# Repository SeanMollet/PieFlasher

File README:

# PieFlasher
Flash NOR and NAND flash chips quickly from a Raspberry PI. Supports 2,3,4,0,0W,0-2
Also supports integration with automated chip flashers.

## Initial setup

### The very beginning
Download the latest version of raspbian-lite and flash to an SD card.

From a freshly installed raspbian-lite

### Configure interfaces
sudo raspi-config
Go to Interfaces and enable I2C and SPI

### Install necessary tools
sudo apt install git python3-pip i2c-tools

### Check the adapter
Run i2cdetect -y 1

If all is working correctly, you'll see:
```
     0  1  2  3  4  5  6  7  8  9  a  b  c  d  e  f
00:                         -- -- -- -- -- -- -- --
10: -- -- -- -- -- -- -- -- -- -- -- -- -- -- -- --
20: -- -- -- -- -- -- -- -- -- -- -- -- -- -- -- 2f
30: -- -- -- -- -- -- -- -- -- -- -- -- 3c -- -- --
40: -- -- -- -- -- -- -- -- -- -- -- -- -- 4d -- --
50: -- -- -- -- -- -- -- -- -- -- -- -- -- -- -- --
60: -- -- -- -- -- -- -- -- -- -- -- -- -- -- -- --
70: -- -- -- -- -- -- -- --
```

### Download and build flashrom

```
git clone https://github.com/flashrom/flashrom
git checkout v.1.3.0

make -j 4
sudo make install
```

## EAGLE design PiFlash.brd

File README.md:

# PieFlasher
Flash NOR and NAND flash chips quickly from a Raspberry PI. Supports 2,3,4,0,0W,0-2
Also supports integration with automated chip flashers.

This software is not secure. The architecture is not secure. The code has some basic sanity checks, but there are countless ways it could be exploited. Don't expose it to the internet. You have been warned.

## Initial setup

### The very beginning
Download the latest version of raspbian-lite and flash to an SD card.

From a freshly installed raspbian-lite

### Configure hostname interfaces
sudo raspi-config
Go to system and then hostname and change the hostname. This name will show up in the flash interface, so make it unique for each device.
Then to go interface options and enable I2C and SPI
Use your favorite text editor to edit /boot/config.txt and edit the i2c_arm line, added the i2c_arm_baudrate part.

```
dtparam=i2c_arm=on,i2c_arm_baudrate=400000

```

Reboot the pi 

```
sudo reboot
```

### Install necessary tools
PieFlasher pre-requisites
```
sudo apt install git python3-pip i2c-tools python3-sphinx python3-venv
```

### Make a venv (Optional)
```
python3 -m venv venv
. venv/bin/activate
pip3 install -r requirements.txt
```

Luma pre-requisites
```
sudo apt install python3-dev libfreetype6-dev libjpeg-dev build-essential
sudo apt install libsdl-dev libportmidi-dev libsdl-ttf2.0-dev libsdl-mixer1.2-dev libsdl-image1.2-dev
```

### Check the adapter
Run i2cdetect -y 1

If all is working correctly, you'll see:
```
     0  1  2  3  4  5  6  7  8  9  a  b  c  d  e  f
00:                         -- -- -- -- -- -- -- --
10: -- -- -- -- -- -- -- -- -- -- -- -- -- -- -- --
20: -- -- -- -- -- -- -- -- -- -- -- -- -- -- -- 2f
30: -- -- -- -- -- -- -- -- -- -- -- -- 3c -- -- --
40: -- -- -- -- -- -- -- -- -- -- -- -- -- 4d -- --
50: -- -- -- -- -- -- -- -- -- -- -- -- -- -- -- --
60: -- -- -- -- -- -- -- -- -- -- -- -- -- -- -- --
70: -- -- -- -- -- -- -- --
```

### The files

Most files in here can be run on their own and will do something useful.

| File | Solo usage |
| gpio.py | Test GPIO inputs/outputs |
| i2c.py | Test I2C ADC and digital POT |
| manualFlash.py | Flash a chip with a given file and voltage |
| power.py | Test the adjustable power supply (DO NOT HAVE A CHIP ATTACHED!)|
| worker_client.py | Connect to server and print messages |

### Running the system

#### Server

Install the pre-requisite python packages as per above on the client devices and on a server. 

The server is run with 

```
python3 server.py
```

It will open port 5000 on all interface. Open this in a browser to see the web interface. It stores log files and image files in data/logs and data/images respectively

#### Client

The client is run with:

```
python3 worker.py
```

The first time it's run it will save a configuration file in data/config. This file specifies the url of the server. Adjust as needed. 

To run the client automatically at startup, copy pieflasher.service to /etc/systemd/system. Edit the file, changing sean and /home/sean to your respective user and path where the repo is stored. Then run:

```
systemd enable pieflasher
```

This will automatically launch PieFlasher at startup and will restart it if it were to fail.

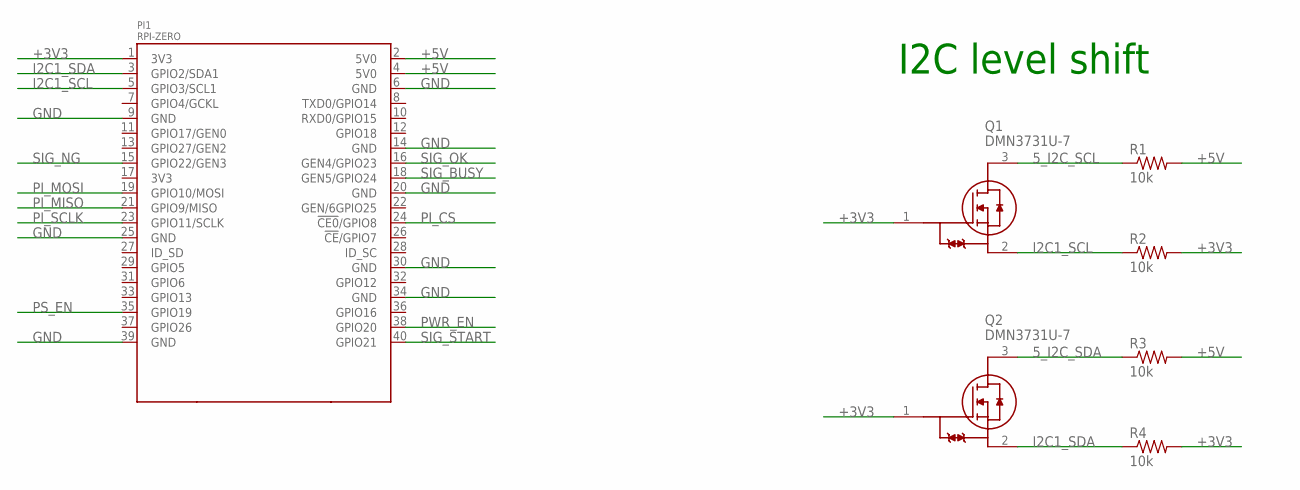
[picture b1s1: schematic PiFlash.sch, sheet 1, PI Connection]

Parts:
PI1: RPI-ZERO; RASPBERRYPI_BASTELSTUBE_V13_RASPI_BOARD_B+_FULL
Q1, Q2: DMN3731U-7; SOT96P240X110-3N
R1, R2, R3, R4: 10k; R0603

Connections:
5_I2C_SCL: Q1.3 (D), R1.1; also elsewhere on the board
5_I2C_SDA: Q2.3 (D), R3.1; also elsewhere on the board
+3V3: PI1.1 (3V3), Q1.1 (G), Q2.1 (G), R2.2, R4.2; also elsewhere on the board
+5V: PI1.2 (5V0), PI1.4 (5V0), R1.2, R3.2; also elsewhere on the board
GND: PI1.6 (GND), PI1.9 (GND), PI1.14 (GND), PI1.20 (GND), PI1.25 (GND), PI1.30 (GND), PI1.34 (GND), PI1.39 (GND); also elsewhere on the board
I2C1_SCL: PI1.5 (GPIO3/SCL1), Q1.2 (S), R2.1; also elsewhere on the board
I2C1_SDA: PI1.3 (GPIO2/SDA1), Q2.2 (S), R4.1; also elsewhere on the board
PI_CS: PI1.24 (!CE0!/GPIO8); also elsewhere on the board
PI_MISO: PI1.21 (GPIO9/MISO); also elsewhere on the board
PI_MOSI: PI1.19 (GPIO10/MOSI); also elsewhere on the board
PI_SCLK: PI1.23 (GPIO11/SCLK); also elsewhere on the board
PS_EN: PI1.35 (GPIO19); also elsewhere on the board
PWR_EN: PI1.38 (GPIO20); also elsewhere on the board
SIG_BUSY: PI1.18 (GEN5/GPIO24); also elsewhere on the board
SIG_NG: PI1.15 (GPIO22/GEN3); also elsewhere on the board
SIG_OK: PI1.16 (GEN4/GPIO23); also elsewhere on the board
SIG_START: PI1.40 (GPIO21); also elsewhere on the board

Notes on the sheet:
I2C level shift

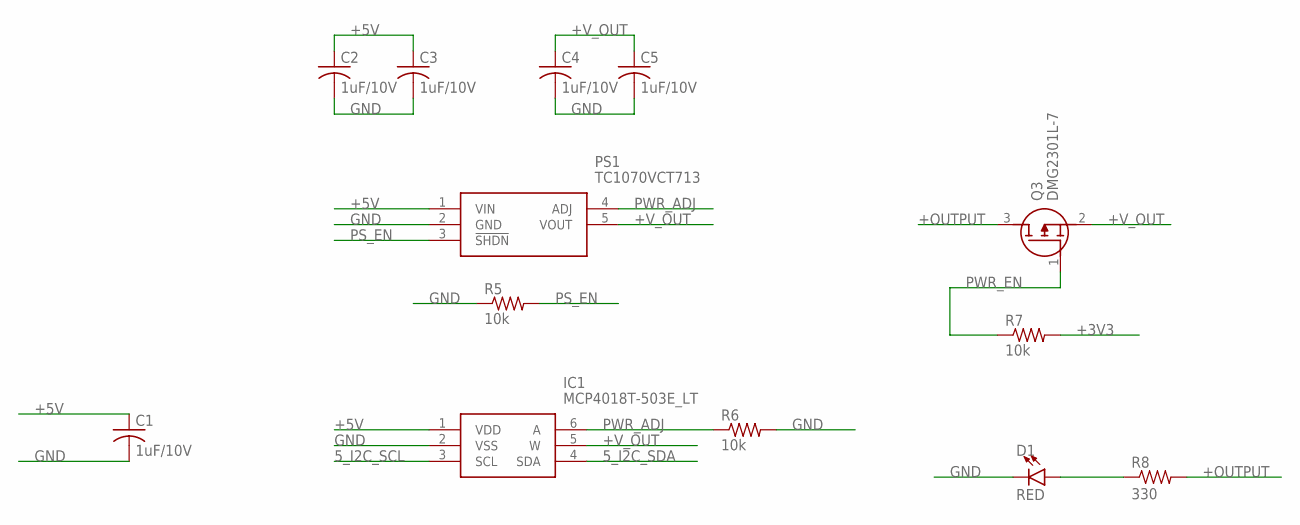
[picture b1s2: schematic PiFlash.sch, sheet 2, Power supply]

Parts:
C1, C2, C3, C4, C5: 1uF/10V; C0603
D1: RED; LED-0402
IC1: MCP4018T-503E_LT; SOT65P210X110-6N
PS1: TC1070VCT713; SOT95P280X145-5N
Q3: DMG2301L-7; SOT96P240X110-3N
R5, R6, R7: 10k; R0603
R8: 330; 0402

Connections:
5_I2C_SCL: IC1.3 (SCL); also elsewhere on the board
5_I2C_SDA: IC1.4 (SDA); also elsewhere on the board
+3V3: R7.2; also elsewhere on the board
+5V: C1.1, C2.1, C3.1, IC1.1 (VDD), PS1.1 (VIN); also elsewhere on the board
+OUTPUT: Q3.3 (D), R8.2; also elsewhere on the board
+V_OUT: C4.1, C5.1, IC1.5 (W), PS1.5 (VOUT), Q3.2 (S); also elsewhere on the board
GND: C1.2, C2.2, C3.2, C4.2, C5.2, D1.C, IC1.2 (VSS), PS1.2 (GND), R5.1, R6.2; also elsewhere on the board
unnamed: D1.A, R8.1
PS_EN: PS1.3 (!SHDN), R5.2; also elsewhere on the board
PWR_ADJ: IC1.6 (A), PS1.4 (ADJ), R6.1
PWR_EN: Q3.1 (G), R7.1; also elsewhere on the board

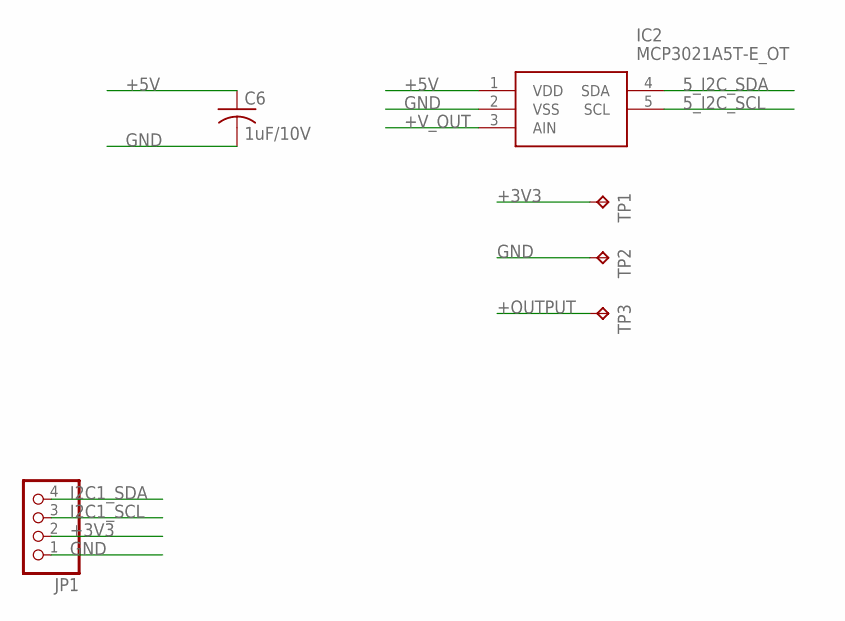
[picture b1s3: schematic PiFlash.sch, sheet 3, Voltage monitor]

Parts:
C6: 1uF/10V; C0603
IC2: MCP3021A5T-E_OT; SOT95P280X145-5N
JP1: PINHD-1X41X04_RND; 1X04_SMALL
TP1: +3v3; TP16R
TP2, TP3: TPTP16R; TP16R

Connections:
5_I2C_SCL: IC2.5 (SCL); also elsewhere on the board
5_I2C_SDA: IC2.4 (SDA); also elsewhere on the board
+3V3: JP1.2, TP1.TP; also elsewhere on the board
+5V: C6.1, IC2.1 (VDD); also elsewhere on the board
+OUTPUT: TP3.TP; also elsewhere on the board
+V_OUT: IC2.3 (AIN); also elsewhere on the board
GND: C6.2, IC2.2 (VSS), JP1.1, TP2.TP; also elsewhere on the board
I2C1_SCL: JP1.3; also elsewhere on the board
I2C1_SDA: JP1.4; also elsewhere on the board

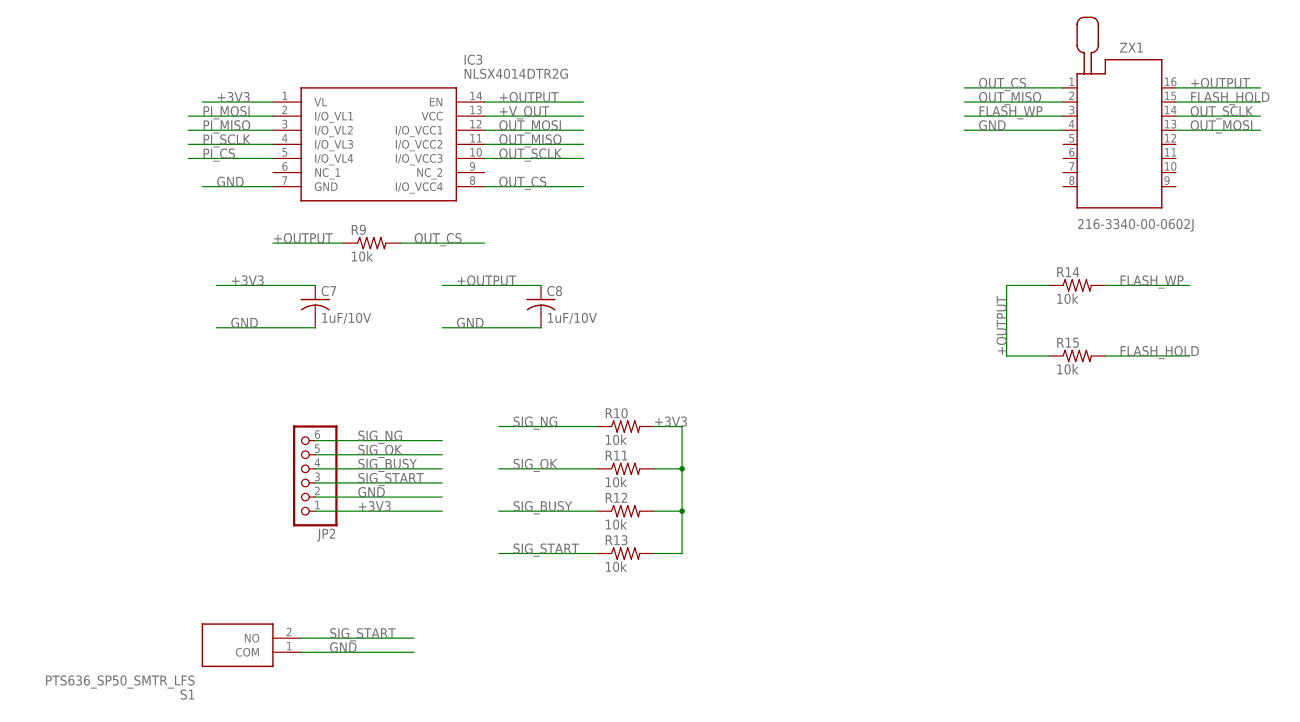
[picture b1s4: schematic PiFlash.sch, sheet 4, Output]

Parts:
C7, C8: 1uF/10V; C0603
IC3: NLSX4014DTR2G; SOP65P640X120-14N
JP2: PINHD-1X6; 1X06
R9, R10, R11, R12, R13, R14, R15: 10k; R0603
S1: PTS636_SP50_SMTR_LFS; PTS636SP50SMTRLFS
ZX1: 216-3340-00-0602J

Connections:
+3V3: C7.1, IC3.1 (VL), JP2.1, R10.2, R11.2, R12.2, R13.2; also elsewhere on the board
+OUTPUT: C8.1, IC3.14 (EN), R9.1, R14.1, R15.1, ZX1.16; also elsewhere on the board
+V_OUT: IC3.13 (VCC); also elsewhere on the board
FLASH_HOLD: R15.2, ZX1.15
FLASH_WP: R14.2, ZX1.3
GND: C7.2, C8.2, IC3.7 (GND), JP2.2, S1.1 (COM), ZX1.4; also elsewhere on the board
OUT_CS: IC3.8 (I/O_VCC4), R9.2, ZX1.1
OUT_MISO: IC3.11 (I/O_VCC2), ZX1.2
OUT_MOSI: IC3.12 (I/O_VCC1), ZX1.13
OUT_SCLK: IC3.10 (I/O_VCC3), ZX1.14
PI_CS: IC3.5 (I/O_VL4); also elsewhere on the board
PI_MISO: IC3.3 (I/O_VL2); also elsewhere on the board
PI_MOSI: IC3.2 (I/O_VL1); also elsewhere on the board
PI_SCLK: IC3.4 (I/O_VL3); also elsewhere on the board
SIG_BUSY: JP2.4, R12.1; also elsewhere on the board
SIG_NG: JP2.6, R10.1; also elsewhere on the board
SIG_OK: JP2.5, R11.1; also elsewhere on the board
SIG_START: JP2.3, R13.1, S1.2 (NO); also elsewhere on the board

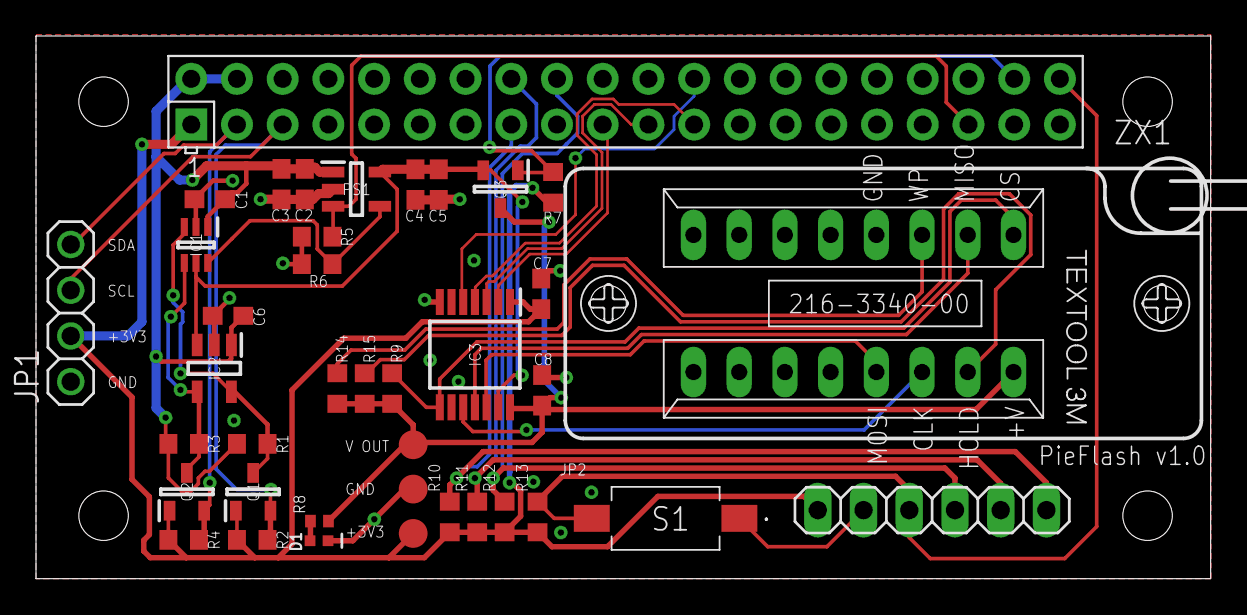
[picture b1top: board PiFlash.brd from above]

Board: 2 copper layers, 65.3 x 30.1 mm, 39 parts (0 on the bottom side), 27 nets.

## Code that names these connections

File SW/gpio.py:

#!/usr/bin/env python3
import RPi.GPIO as GPIO
import threading
from time import sleep
from typing import Callable


class pi_gpio:
    def __init__(self) -> None:
        GPIO.setmode(GPIO.BCM)
        # ("Pin name", GPIO #, Initial value)
        self.pins = {}
        self.pins["SIG_NG"] = (22, True, GPIO.OUT)
        self.pins["SIG_OK"] = (23, True, GPIO.OUT)
        self.pins["SIG_BUSY"] = (24, True, GPIO.OUT)
        self.pins["SIG_START"] = (21, True, GPIO.IN)
        self.pins["PS_EN"] = (19, False, GPIO.OUT)
        self.pins["PWR_EN"] = (20, True, GPIO.OUT)

        for name in self.pins:
            pin = self.pins[name]
            # print("Setting up",name,"GPIO:",pin[0],"default:",pin[1])
            if pin[2] == GPIO.OUT:
                GPIO.setup(pin[0], GPIO.OUT)
                GPIO.output(pin[0], pin[1])
            else:
                GPIO.setup(pin[0], GPIO.IN, pull_up_down=GPIO.PUD_UP)

    def setPin(self, pin: str, value: bool):
        if self.pins[pin] is not None and self.pins[pin][2] == GPIO.OUT:
            GPIO.output(self.pins[pin][0], value)

    def getPin(self, pin: str) -> bool:
        if self.pins[pin] is not None and self.pins[pin][2] == GPIO.IN:
            return GPIO.input(self.pins[pin][0])

    def waitForEdge(self, pin: str, state: bool) -> None:
        if self.pins[pin] is not None and self.pins[pin][2] == GPIO.IN:
            if state:
                return GPIO.wait_for_edge(self.pins[pin][0], GPIO.RISING)
            else:
                return GPIO.wait_for_edge(self.pins[pin][0], GPIO.FALLING)

    def callOnEdge(self, pin: str, state: bool, callback: Callable) -> None:
        if self.pins[pin] is not None and self.pins[pin][2] == GPIO.IN:
            if state:
                GPIO.add_event_detect(
                    self.pins[pin][0],
                    GPIO.RISING,
                    callback=callback,
                    bouncetime=300,
                )
            else:
                GPIO.add_event_detect(
                    self.pins[pin][0],
                    GPIO.FALLING,
                    callback=callback,
                    bouncetime=300,
                )

    def defaultPin(self, pin: str):
        if self.pins[pin] is not None:
            GPIO.output(self.pins[pin][0], self.pins[pin][1])

    def pinIsOutput(self, pin: str) -> bool:
        if self.pins[pin] is not None:
            return self.pins[pin][2] == GPIO.OUT
        return False

    def setSigNG(self, value: bool) -> None:
        self.setPin("SIG_NG", value)

    def setSigOK(self, value: bool) -> None:
        self.setPin("SIG_OK", value)

    def setSigBusy(self, value: bool) -> None:
        self.setPin("SIG_BUSY", value)

    def getSigStart(self) -> None:
        return self.getPin("SIG_START")

    def setPsEn(self, value: bool) -> None:
        self.setPin("PS_EN", value)

    def setPwrEn(self, value: bool) -> None:
        self.setPin("PWR_EN", not value)

    def holdSignalWorker(self, signal, delay):
        self.setPin(signal, False)
        sleep(delay)
        self.setPin(signal, True)

    def holdSignal(self, signal, delay) -> None:
        threading.Thread(target=self.holdSignalWorker, args=[signal, delay]).start()

    def waitSigStart(self) -> None:
        self.waitForEdge("SIG_START", False)

    def callOnSigStart(self, callback: Callable) -> None:
        self.callOnEdge("SIG_START", False, callback)


if __name__ == "__main__":
    print("Initializing GPIO")
    gpio = pi_gpio()

    print("IO pin testing")
    pins = ["SIG_NG", "SIG_OK", "SIG_BUSY", "SIG_START"]
    for pin in pins:
        if gpio.pinIsOutput(pin):
            print("Setting", pin, "high, press enter to lower")
            gpio.setPin(pin, True)
            input()
            print("Press enter to set", pin, "low")
            input()
            gpio.setPin(pin, False)
            print("Press enter to continue")
            input()
            gpio.defaultPin(pin)
        else:
            value = gpio.getPin(pin)
            print("Value of", pin, "is:", value, "Press enter to check again")
            input()
            value = gpio.getPin(pin)
            print("Value of", pin, "is:", value, "Press enter to continue")

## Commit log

2023-07-23 Initial checkin
2023-07-23 Added GPL 2 license
2023-07-23 Creating readme
2023-07-23 Rename readme so it renders as markdown
2023-07-23 Update readme, add first software files
2023-07-23 Adding gpio
2023-07-23 Can read the Analog and set the pot. HW works as intended
2023-07-23 Checking the output control transistor. It doesn't work. :( Oh well, ps_en works a mint, so we'll just use that
2023-07-23 Remove that test. We know it doesn't work.
2023-07-23 Removed debugging from gpio Added power, which turns on 3.3 and was used to test with a real chip (worked) Also, the +OUTPUT fet does work as long as +VOUT isn't too high (below about 4V). That's goo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
2023-07-23 Add a data folder and a .keep
2023-07-23 Don't commit things in the data directory
2023-07-23 Hide the inverted nature of Power enable
2023-07-23 Switch to CamelCase, adjust PowerEn to work the new way
2023-07-23 Split up power into testing functions
2023-07-23 Basic configuration loader/saver
2023-07-23 Add shebang to startup, add flask
2023-07-23 Add a tolerance to voltages
2023-07-23 Ignore Joe's backup files
2023-07-23 Add a mutex to i2c. Will have to add the oled to this as well
2023-07-23 Finish name change
2023-07-23 We now have a handy power supply tester in power.py, no need to also have it in i2c
2023-07-23 Add a few more comments to power.py
2023-07-23 Remove the .keep, I can just create the folders as needed
2023-07-23 Add another launch for testing
2023-07-23 Flash file that interacts with flashrom
2023-07-23 Command line flashing
2023-07-23 Utilities file
2023-07-23 Minor refactors and fixing exception handling
2023-07-23 Create the folder structure on the fly
2023-07-23 Add socketio
2023-07-23 Use the config path for config files!
2023-07-24 Add logfile names
2023-07-24 Up the SPI speed, track size
2023-07-24 Make manualflash actually work
2023-07-24 When a logfile is ordered, spawn a thread that reads/parses it. This will update percentages, process, etc..
2023-07-24 Formatted
2023-07-24 Testing to see how often we receive
2023-07-24 Reformat a little Non blocking works like a champ, we see the progress. So, we can have a nice progress bar
2023-07-24 Format the others
2023-07-24 Added a progress bar to manualFlash based on output of Flashrom. Works for erasing and flashing. So nice to have a bar...
2023-07-24 Added voltage calibration spreadsheet
2023-07-24 Oled now uses the i2c mutex Neat little display shaping up
2023-07-24 Initial testing/setup of the working and the Oled
2023-07-24 Startup logo
2023-07-24 Fix vertical scaling on the pie
2023-07-24 Fix SIG_START
2023-07-24 Take command line options for file and voltage
2023-07-24 Change to using ImageDraw for the main render, so it can also use lockI2C
2023-07-24 Scroll the filename, looks slick!
2023-07-24 Flashing works on the screen!
2023-07-24 Added tracking of reading and verifying statuses. Works pretty darn good. Now to the web interface
2023-07-24 Webserver - WIP
2023-07-24 Don't install the PI stuff on a non-Linux box. This might need to be made smarter later. Good enough for now
2023-07-24 Add websocket client
2023-07-24 WS testing works very well. I'm impressed with how well socket-io and the python WS client work.
2023-07-24 Make the worker client work. Impressive how well it does work..
2023-07-24 Logging works, sending filenames works. Now to implement the GUI
2023-07-24 Remote logging works
2023-07-25 Add a ping every 10 seconds so the server knows we're alive Clean up shutdown
2023-07-25 Send status to the server regularly
2023-07-25 WiP: web interface for the server
2023-07-25 WIP: Web interface
2023-07-25 Fix the conditions in requirements
2023-07-25 Shutdown clean if we reconnect while shutting down
2023-07-25 Add the hostname to the Idle display
2023-07-25 Use the actual hostname
2023-07-25 Add reboot command
2023-07-25 Delay the reboot by 2 seconds so we can see it on the screen
2023-07-25 Oops.. forgot a :
2023-07-25 Let's pass this up so we can actually show the reboot status
2023-07-25 Move those down..
2023-07-25 Send an update once we've applied a file change
2023-07-25 String this first
2023-07-25 WiP: more control commands
2023-07-25 Rework ping and connect so we always know what it is
2023-07-25 Reformat the voltages Always send the register again
2023-07-25 Send the state name without the class
2023-07-25 Getting there on the web interface
2023-07-25 Upload works and also won't let you overwrite. I'm purposely not creating a delete here, since it's all files anyway, the user can easily clean things up
2023-07-25 Add a timestamp to the files
2023-07-25 WiP: Chosing a flash configuration
2023-07-25 Flashing selection works. Now to make the little buggers download the file
2023-07-25 Changed file renaming to use - instead of ( so it complies with secure_filename Files are now available on the server, time to make the client download
2023-07-25 Download the file to a tmpfs when sent a new one. Works!
2023-07-25 Add the I/O interface controls for the flashing robot
2023-07-25 Add a favicon so it shows up on Android
2023-07-25 Add security notice
2023-07-25 We can go ahead and actually shutdown on shutdown now
2023-07-25 Let's try this again, instead of messing up the sigint
2023-07-25 Let's not make a recursive call to shutdown..
2023-07-26 Send logs Refactor shutdown a bit so we don't do it accidentally
2023-07-26 Split server connection out to a thread so it will run forever trying to connect
2023-07-26 Cleanup config, dedup status messages
2023-07-26 Split logging and statusData Fix logging so it actually works
2023-07-26 Split logging and statusData
2023-07-26 Let's actually send the status message..
2023-07-26 Remove the ping/pong from the client, no real need for that. Instead, let's periodically send status messages
2023-07-26 Might as well send status while downloading too
2023-07-26 Don't spam download status updates
2023-07-26 Send even fewer download updates
2023-07-26 Send a few more, but with a larger chunk
2023-07-26 Moved status to be WS based. Works really well
2023-07-26 Log viewers
2023-07-26 WiP: Live logging
2023-07-26 Works better when we turn log sending back on...
2023-07-26 Scrolling works well now
2023-07-26 Live logs now loads the current file from disk, then picks up with WS. There's a small chance to loose a line, but that's acceptable
2023-07-26 Add shutdown and reboot buttons
2023-07-26 Added systemd service for pieflasher
2023-07-26 Remove test code
2023-07-26 Additional documentation, minor cleanup of filenames
2023-07-26 Add systemd for the server as well
2023-07-26 Allow the server to run with the dev webserver. This shouldn't ever have enough clients or be exposed to the internet, so there's little justification for a heavier server. Don't expose it to the int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
2023-07-26 Let's actually save the config file
2023-07-26 Tinkering
2023-07-26 Unbuffer STDOUT and STDERR so systemd works better
2023-07-26 Add rotation option
2023-07-26 Cleanup
2023-07-26 Return the new default value. Also default rotation to 0
2023-07-26 Having a strange pathing issue.. trying this
2023-07-26 Don't download a bad response
2023-07-26 Trying this
2023-07-26 Log the data path
2023-07-26 More detail
2023-07-26 Formallly uuse the cwd as the base
2023-07-26 Let's be smarter about this path thing..
2023-07-26 Missed a detail
2023-07-26 No need to log this to syslog as well
2023-07-26 Send a status message back for reboot/shutdown
2023-07-26 Doesn't work so well sending that message after we disconnect
2023-07-27 Re-worked this to have multiple timers. Never going to get used though, because the PI supports GPIO Interrupts!
2023-07-27 GPIO Interrupt glory
2023-07-27 This should work, but it doesn't trigger. Not sure why
2023-07-27 There we go.. interrupting gpio bliss!
2023-07-27 When viewing live logs, if we loaded one from the server, show the name
2023-07-27 Clear up race condition with flashes that go faster than we can read the log
2023-07-27 Don't overwrite our filename with the open file
2023-07-27 Adding an erase option
2023-07-27 Properly show erase in the list
2023-07-27 Add a space and a -
2023-07-27 Send a final status message at the end of the flash
2023-07-27 Reworked logging to be a class. Changed to using my version of flashrom that supports appending
2023-07-27 Added new dependency for main branch flashrom
2023-07-27 Reworking logging shutdown
2023-07-27 Show erase on the button
2023-07-27 Fix the title on the log viewer
2023-07-27 Working on parsers for new flashrom
2023-07-27 Appending flashrom is the real ticket to success here. Works much better now.
2023-07-27 Update the erase state
2023-07-27 Disable verification on erase (doesn't actually work though) Cleanup callback a bit
2023-07-27 Slow down the SPI to see if maybe that's my issue
2023-07-27 Wait just a hair longer before probing
2023-07-27 OK, speed doesn't seem to be the problem
2023-07-27 Must use raspi-config to enable spi
2023-07-27 Teach power some new tricks
2023-07-27 Get the parens in the right spot
2023-07-27 Log voltage settings and wait a little longer for stability
2023-07-27 Wait after turning on the FET Check the voltage before we kick off for the flash
2023-07-27 Fix the print
2023-07-27 Let's try that again calling the instance and not the class
2023-07-27 Allow calibration/offsetting the voltage in config
2023-07-27 Forgot to global that
2023-07-27 Loop on chip detection since it sometimes takes a while
2023-07-27 Print the pot value, makes it easier to adjust
2023-07-27 Up the scan count and slow down the SPI a bit
2023-07-27 Those shouldn't have ended up in here
2023-07-27 More pos parser earlier so it will catch Erases
2023-07-27 Slow it down quite a bit more
2023-07-28 Check the size too
2023-07-28 Works better with an OR. :-P
2023-07-28 Working back to older version of flashrom
2023-07-28 Use home directory for datadir Revert to older flashrom Don't round the value we use to validate in power
2023-07-28 Works pretty well, good enough for now
2023-07-28 Slow it down a touch
2023-07-28 slower yet
2023-07-28 If we get an ERASE FAILED, kill the flash and let it get restarted
2023-07-31 Exit if we never saw the logfile Check for the updateFunc everytime we try to use it
2023-07-31 Don't save log files
2023-07-31 Scan now adjusts speed upwards to find the maximum we can use
2023-07-31 Use the new speed test scanner from worker
2023-07-31 Add a few more possible speeds. Not likely to ever get to use them, but might as well have them in here.
2023-07-31 Addeding Latest result to status
2023-07-31 Restart failed flashes at lower speed
2023-07-31 Oops, extra ,
2023-07-31 Include speed in status while flashing
2023-08-09 Catch EW as well
2023-08-31 Increase the retry count. They don't take that long anyway
2023-08-31 Fewer speeds and drop faster
2024-03-14 Add requests
2024-03-14 Moving to python based flashing
2024-03-14 Flashes nicely
2024-03-15 Works! Need to double check, but I'm feeling positive
2024-03-15 Removed flashrom - uses internal flashing mechanism now It works decently well, could be made faster, but we don't need faster at the moment
2024-03-15 Don't hang up if the chip doesn't ID the first time
2024-03-15 Print failing IDs
2024-03-15 Turn down the voltage a touch
2024-03-15 Make flashing smarter
2024-03-15 Fail if couldn't find a chip
2024-03-15 Print the signalling so it's easier to follow on screen
2024-03-15 Slow down
2024-03-15 Probe at lower speed
2024-03-15 A little extra juice
2024-03-15 Try sleeping for a bit first
2024-03-15 Works like a charm on the desk, must be a machine issue
2024-03-15 ID even slower
2024-03-15 Don't try as many times
2024-03-26 Add another Winbond chip
2024-05-02 Works with FTDI USB flasher now
2024-05-02 Make FTDI Optional
2024-05-07 Don't worry about power on system using FTDI flashing, since it doesn't power the chip anyway.
2024-05-07 Typo
2024-08-13 Increase the frequency.. should work
2024-08-13 Testing
2024-08-13 Faster logging and let's try 32KB sectors
2024-08-13 More tinkering
2024-08-13 More data

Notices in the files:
parts and their libraries:
SparkFun-LED: Licensing: Creative Commons ShareAlike 4.0 International - https://creativecommons.org/licenses/by-sa/4.0
